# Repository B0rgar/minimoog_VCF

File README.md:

Thomas henry 555 vco with panel. based on Eagleproject from Gerbster.nl.

imported to kicad. IO board redesigned for a more logical layout and extra audio and CV input.

PCBS ordered from JLCPCB. will update after building and testing.

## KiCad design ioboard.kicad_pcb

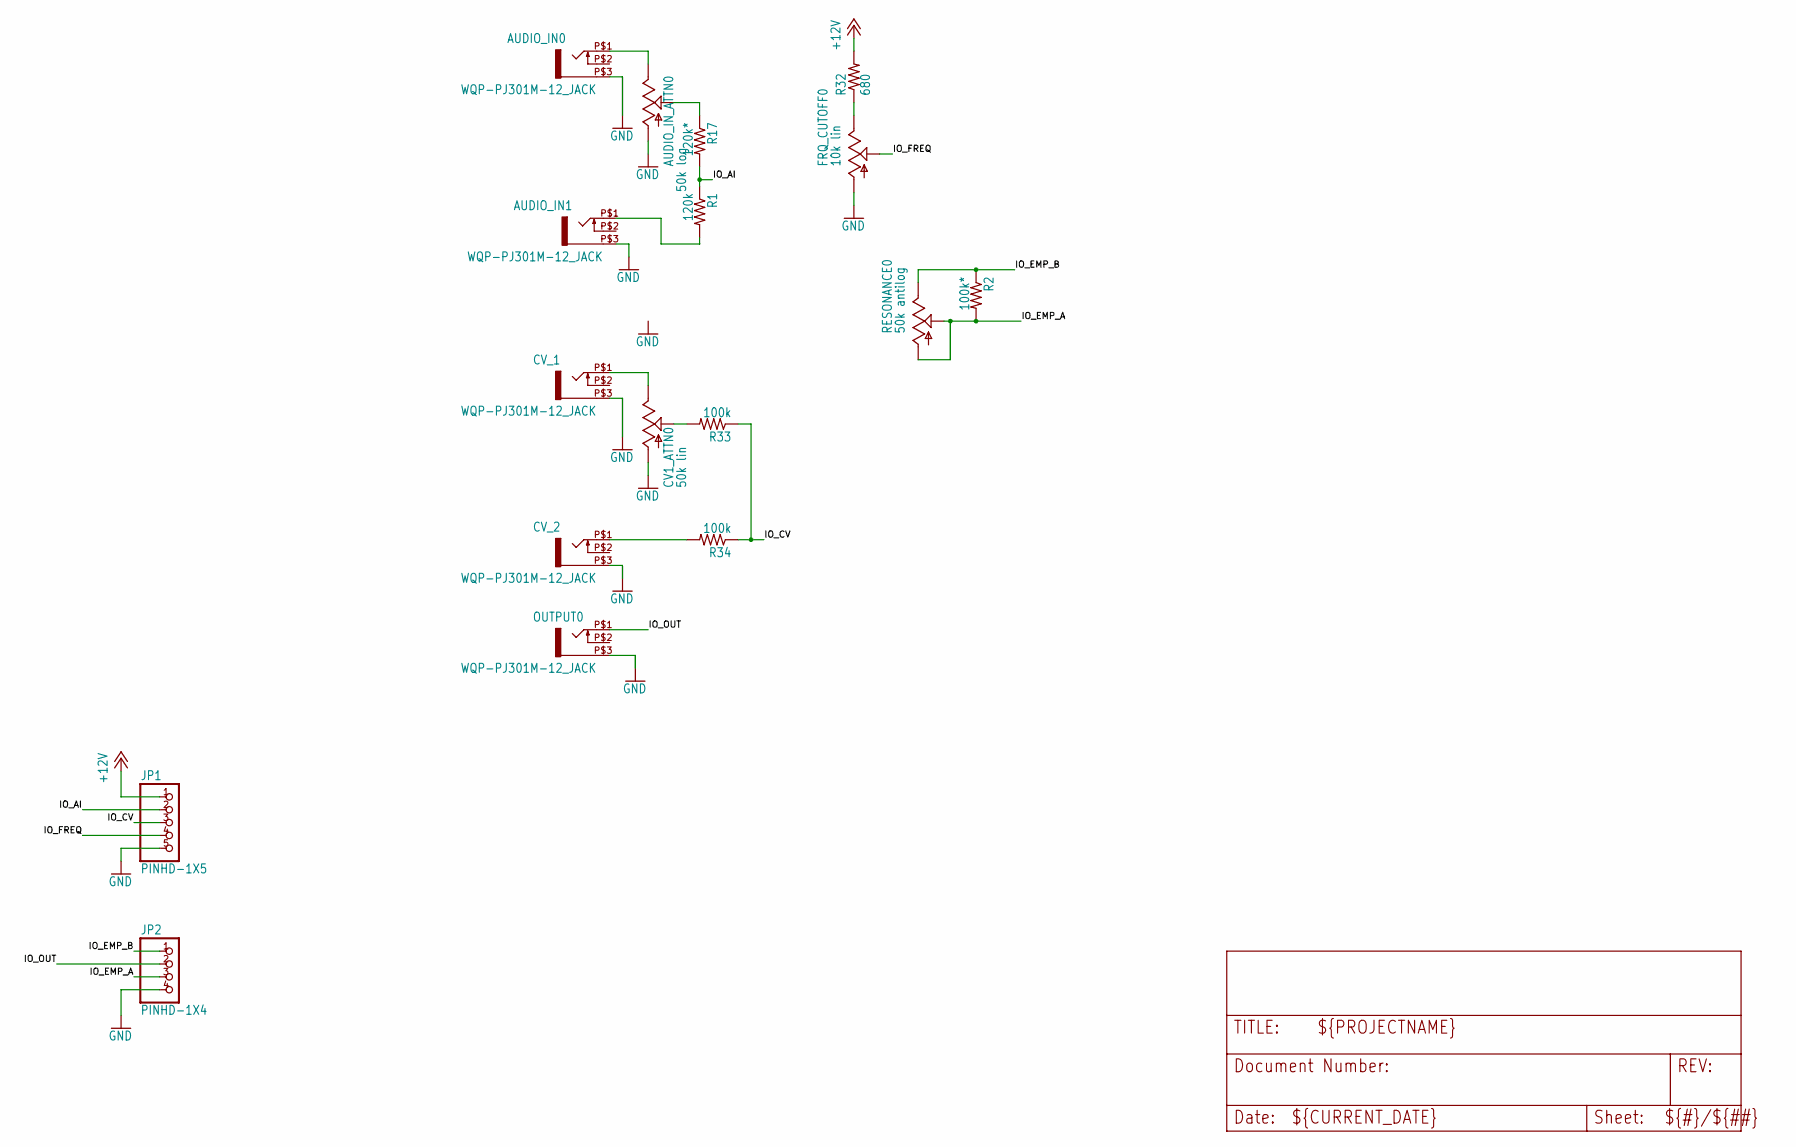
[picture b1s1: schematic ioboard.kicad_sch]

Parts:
AUDIO_IN0, AUDIO_IN1: WQP-PJ301M-12_JACK
AUDIO_IN_ATTN0: 50k log; EVUF
CV1_ATTN0: 50k lin; EVUF
CV_1, CV_2: WQP-PJ301M-12_JACK
FRQ_CUTOFF0: 10k lin; EVUF
JP1: PINHD-1X5; 1X05
JP2: PINHD-1X4; 1X04
OUTPUT0: WQP-PJ301M-12_JACK
R1: 120k; 0204_7
R2: 100k*; 0204_7
R17: 120k*; 0204_7
R32: 680; 0204_7
R33, R34: 100k; 0204_7
RESONANCE0: 50k antilog; EVUF

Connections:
+12V: JP1.1, R32.2
/IO_AI: JP1.2, R1.1, R17.2
/IO_CV: JP1.3, R33.1, R34.1
/IO_EMP_A: JP2.3, R2.2, RESONANCE0.1 (A), RESONANCE0.2 (S)
/IO_EMP_B: JP2.1, R2.1, RESONANCE0.3 (E)
/IO_FREQ: FRQ_CUTOFF0.2 (S), JP1.4
/IO_OUT: JP2.2, OUTPUT0.P$1 (2)
GND: AUDIO_IN0.P$3 (1), AUDIO_IN1.P$3 (1), AUDIO_IN_ATTN0.1 (A), CV1_ATTN0.1 (A), CV_1.P$3 (1), CV_2.P$3 (1), FRQ_CUTOFF0.1 (A), JP1.5, JP2.4, OUTPUT0.P$3 (1)
unnamed: AUDIO_IN0.P$1 (2), AUDIO_IN_ATTN0.3 (E)
unnamed: AUDIO_IN1.P$1 (2), R1.2
unnamed: AUDIO_IN_ATTN0.2 (S), R17.1
unnamed: CV1_ATTN0.3 (E), CV_1.P$1 (2)
unnamed: CV1_ATTN0.2 (S), R33.2
unnamed: CV_2.P$1 (2), R34.2
unnamed: FRQ_CUTOFF0.3 (E), R32.1

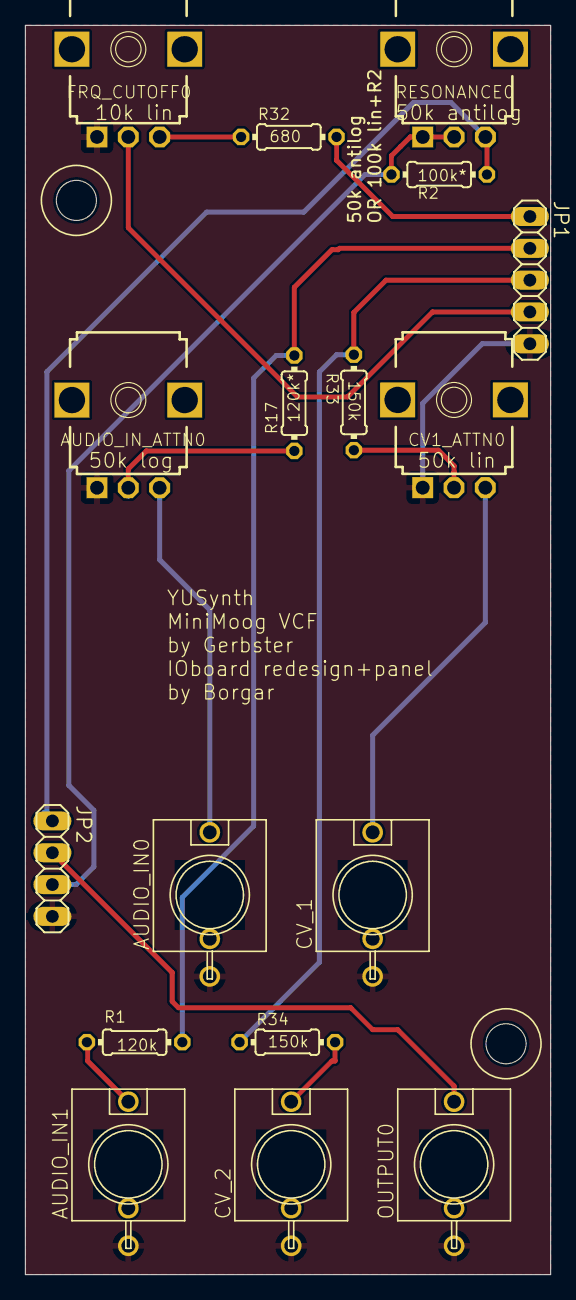
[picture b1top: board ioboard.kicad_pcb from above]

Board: 2 copper layers, 41.9 x 99.7 mm, 19 parts (0 on the bottom side), 15 nets.

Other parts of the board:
@HOLE0, @HOLE1: (no value)

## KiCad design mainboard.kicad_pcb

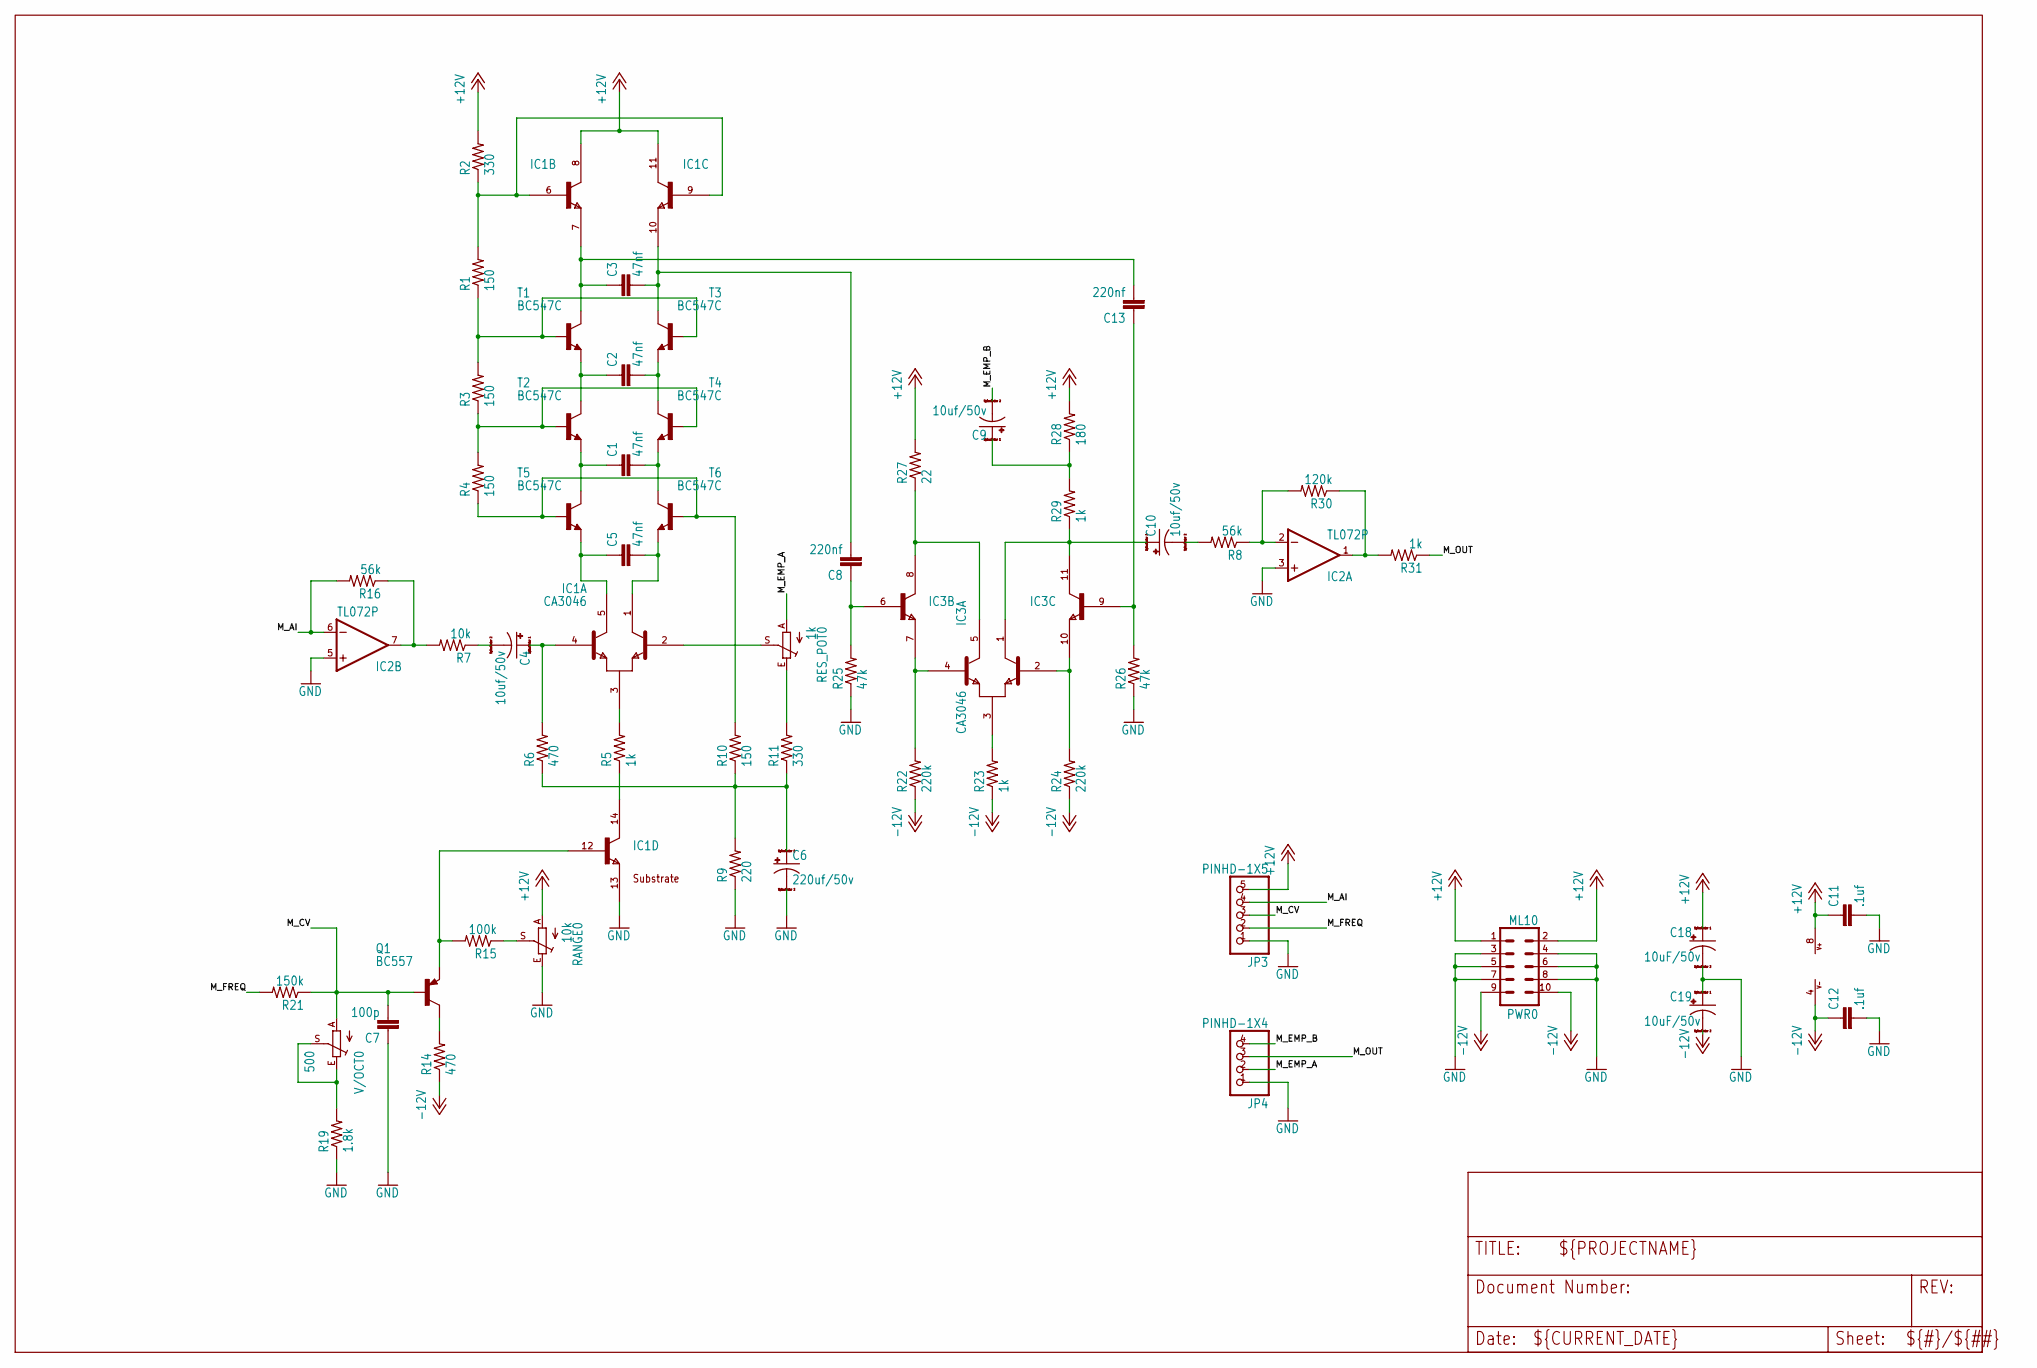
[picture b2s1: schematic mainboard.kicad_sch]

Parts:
C1, C2, C3, C5: 47nf; C050-024X044
C4, C9, C10: 10uf/50v; E2,5-5
C6: 220uf/50v; E3,5-10
C7: 100p; C050-024X044
C8, C13: 220nf; C050-024X044
C11, C12: .1uf; C050-024X044
C18, C19: 10uF/50v; E2,5-6
IC1, IC3: CA3046; DIL14
IC2: TL072P; DIL08
JP3: PINHD-1X5; 1X05
JP4: PINHD-1X4; 1X04
PWR0: ML10
Q1: BC557; TO92-EBC
R1, R3, R4, R10: 150; 0204_7
R2, R11: 330; 0204_7
R5, R23, R29, R31: 1k; 0204_7
R6, R14: 470; 0204_7
R7: 10k; 0204_7
R8, R16: 56k; 0204_7
R9: 220; 0204_7
R15: 100k; 0204_7
R19: 1.8k; 0204_7
R21: 150k; 0204_7
R22, R24: 220k; 0204_7
R25, R26: 47k; 0204_7
R27: 22; 0204_7
R28: 180; 0204_7
R30: 120k; 0204_7
RANGE0: 10k; CA9V
RES_POT0: 1k; CA9V
T1, T2, T3, T4, T5, T6: BC547C; TO92-CBE
V/OCT0: 500; S64YW

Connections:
+12V: C11.1, C18.+, IC1.8 (C), IC1.11 (C), IC2.8 (V+), JP3.5, PWR0.1, PWR0.2, R2.2, R27.2, R28.2, RANGE0.A
-12V: C12.1, C19.-, IC2.4 (V-), PWR0.9, PWR0.10, R14.1, R22.1, R23.1, R24.1
GND: C6.-, C7.1, C11.2, C12.2, C18.-, C19.+, IC1.13 (E), IC2.3 (+IN), IC2.5 (+IN), JP3.1, JP4.1, PWR0.3, PWR0.4, PWR0.5, PWR0.6, PWR0.7, PWR0.8, R9.1, R19.1, R25.1, R26.1, RANGE0.E
M_AI: IC2.6 (-IN), JP3.4, R16.2
M_CV: C7.2, JP3.3, Q1.B, R21.1, V/OCT0.A
M_EMP_A: JP4.2, RES_POT0.A
M_EMP_B: C9.-, JP4.4
M_FREQ: JP3.2, R21.2
M_OUT: JP4.3, R31.1
unnamed: C5.1, IC1.5 (C2), T5.E
unnamed: IC1.6 (B), IC1.9 (B), R1.2, R2.1
unnamed: C3.1, C13.2, IC1.7 (E), T1.C
unnamed: C3.2, C8.2, IC1.10 (E), T3.C
unnamed: C2.1, T1.E, T2.C
unnamed: C2.2, T3.E, T4.C
unnamed: C1.1, T2.E, T5.C
unnamed: C1.2, T4.E, T6.C
unnamed: R1.1, R3.2, T1.B, T3.B
unnamed: R3.1, R4.2, T2.B, T4.B
unnamed: R4.1, R10.2, T5.B, T6.B
unnamed: C5.2, IC1.1 (C1), T6.E
unnamed: IC1.3 (E), R5.2
unnamed: IC1.14 (C), R5.1
unnamed: C4.+, IC1.4 (B2), R6.2
unnamed: C4.-, R7.1
unnamed: C6.+, R6.1, R9.2, R10.1, R11.1
unnamed: IC2.7 (OUT), R7.2, R16.1
unnamed: R19.2, V/OCT0.E, V/OCT0.S
unnamed: IC1.12 (B), Q1.E, R15.2
unnamed: IC1.2 (B1), RES_POT0.S
unnamed: R11.2, RES_POT0.E
unnamed: C13.1, IC3.9 (B), R26.2
unnamed: Q1.C, R14.2
unnamed: R15.1, RANGE0.S
unnamed: C10.-, R8.2
unnamed: IC3.4 (B2), IC3.7 (E), R22.2
unnamed: IC3.3 (E), R23.2
unnamed: IC3.2 (B1), IC3.10 (E), R24.2
unnamed: IC3.5 (C2), IC3.8 (C), R27.1
unnamed: C10.+, IC3.1 (C1), IC3.11 (C), R29.1
unnamed: C9.+, R28.1, R29.2
unnamed: IC2.1 (OUT), R30.1, R31.2
unnamed: C8.1, IC3.6 (B), R25.2
unnamed: IC2.2 (-IN), R8.1, R30.2

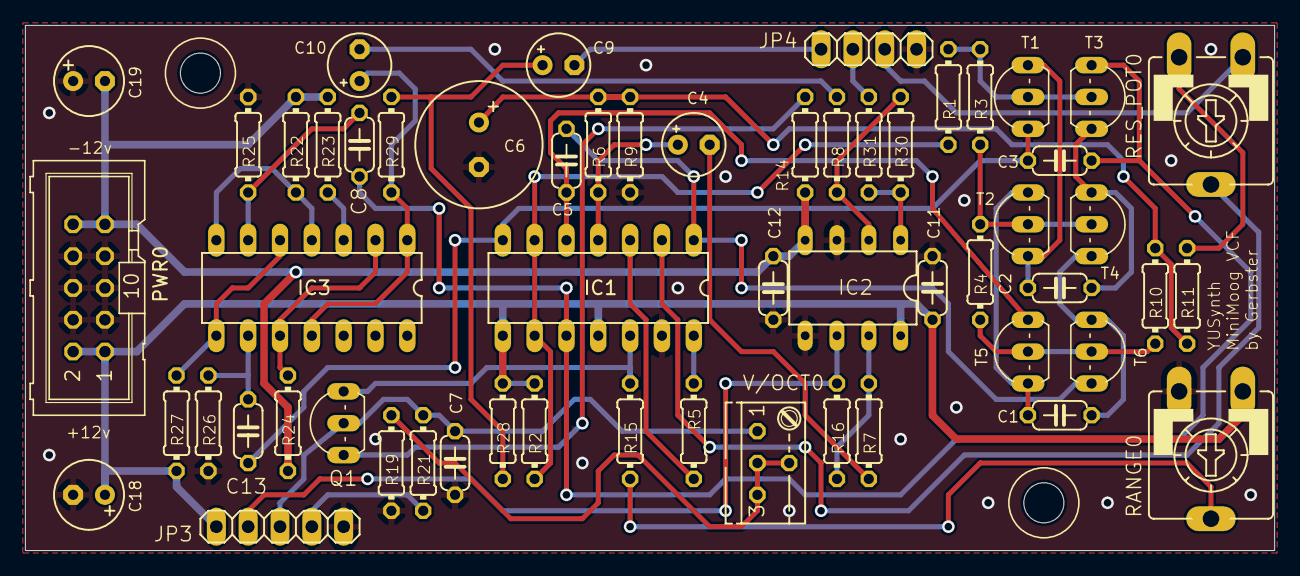
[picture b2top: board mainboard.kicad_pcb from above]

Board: 2 copper layers, 99.7 x 41.9 mm, 59 parts (0 on the bottom side), 44 nets.

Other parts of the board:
@HOLE0, @HOLE1: (no value)

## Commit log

2025-03-16 last commit
2025-03-16 pics
